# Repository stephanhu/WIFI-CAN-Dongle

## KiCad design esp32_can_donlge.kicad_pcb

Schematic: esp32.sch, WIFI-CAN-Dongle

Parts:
C1, C2, C4: 100n/25V; C_0603_1608Metric
C3, C5: 10u/25V; C_0805_2012Metric
C6, C7: C; C_0603_1608Metric
D1, D2: LED; LED_0805_2012Metric
D3: BAT54C; SOT-23
J1: Conn_01x02_Male; PinHeader_1x02_P2.54mm_Horizontal
J2: DM3AT-SF-PEJM5(40); microSD_HC_Hirose_DM3AT-SF-PEJM5
L1, L2: L; L_0603_1608Metric
Q1: DMG2305UX-7; SOT-23
R1, R2: 1k; R_0603_1608Metric
R3, R4, R5, R6, R7, R8, R15: 10k; R_0603_1608Metric
R9, R11, R12, R13: 33R; R_0603_1608Metric
R10: 10R; R_0603_1608Metric
R14: 200R; R_0603_1608Metric
R16, R17: 220R; R_0603_1608Metric
U1: ESP32-WROOM-32
Y1: LFXTAL009709Bulk; Crystal_SMD_3215-2Pin_3.2x1.5mm

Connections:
+3V3: C4.1, C5.1, Q1.2, R3.1, R4.2, U1.2; also elsewhere on the board
/can_interface/CAN_EN: U1.12; also elsewhere on the board
/can_interface/CAN_RX: R16.2; also elsewhere on the board
/can_interface/CAN_TERM_EN: U1.6; also elsewhere on the board
/can_interface/CAN_TX: R17.2; also elsewhere on the board
/esp32/BOOT: D3.1, J1.1, U1.25
/esp32/DET_A: J2.10, U1.27, U1.37
/esp32/DET_B: R15.2, U1.10, U1.28
/esp32/ESP_EN: C1.1, R3.2, U1.3; also elsewhere on the board
/esp32/IO0: D3.3; also elsewhere on the board
/esp32/SD_CLK: R10.1, U1.13
/esp32/SD_CMD: R6.2, R13.1, U1.23
/esp32/SD_DAT0: R7.2, R14.1, U1.24
/esp32/SD_DAT1: R8.2, R11.1, U1.26
/esp32/SD_DAT2: D3.2, R12.1, U1.14
/esp32/SD_DAT3: R5.2, R9.1, U1.16
/esp32/SD_EN: Q1.1, R4.1, U1.11
/esp32/SD_VDD: C2.1, C3.1, J2.4, L1.1, R5.1, R6.1, R7.1, R8.1
/esp32/TEST_LED0: R1.1, U1.30
/esp32/TEST_LED1: R2.1, U1.31
/usb_uart/RXD: U1.35; also elsewhere on the board
/usb_uart/TXD: U1.34; also elsewhere on the board
BAT_ADC_IN: U1.7; also elsewhere on the board
GND: C1.2, C2.2, C3.2, C4.2, C5.2, C6.1, C7.1, D1.1, D2.1, J1.2, J2.6, L2.1, U1.1, U1.15, U1.38, U1.39; also elsewhere on the board
unnamed: C6.2, U1.8, Y1.1
unnamed: C7.2, U1.9, Y1.2
unnamed: D1.2, R1.2
unnamed: D2.2, R2.2
unnamed: J2.1, R12.2
unnamed: J2.2, R9.2
unnamed: J2.3, R13.2
unnamed: J2.5, R10.2
unnamed: J2.7, R14.2
unnamed: J2.8, R11.2
unnamed: J2.9, R15.1
unnamed: J2.11, L2.2
unnamed: L1.2, Q1.3
unnamed: R16.1, U1.33
unnamed: R17.1, U1.36

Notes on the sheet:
0: SPI Boot 1: Download Boot
using two pins for lower quiescent current
Global Label
Hierachical Label
Local Label
activate internal pullup in user programm on GPIO12

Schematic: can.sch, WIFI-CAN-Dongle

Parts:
C8: 100n/25V; C_0603_1608Metric
C9: 10u/25V; C_0805_2012Metric
R18: 0R; R_0603_1608Metric
R19, R20: 10k; R_0603_1608Metric
R21: 1k; R_0603_1608Metric
R22: 470R; R_0603_1608Metric
R23: 100R; R_0603_1608Metric
U2: SN65HVD230DR; SOIC-8_3.9x4.9mm_P1.27mm
U3: TLP175A; MFSOP6-4_4.4x3.6mm_P1.27mm

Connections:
+3V3: C8.1, C9.1, R19.1, R21.1, U2.3; also elsewhere on the board
/can_interface/CAN_EN: R18.2; also elsewhere on the board
/can_interface/CAN_N: U2.6, U3.4; also elsewhere on the board
/can_interface/CAN_P: R23.1, U2.7; also elsewhere on the board
/can_interface/CAN_RX: U2.4; also elsewhere on the board
/can_interface/CAN_TERM_EN: R22.2; also elsewhere on the board
/can_interface/CAN_TX: U2.1; also elsewhere on the board
GND: C8.2, C9.2, R20.2, U2.2, U3.3; also elsewhere on the board
unnamed: R18.1, R21.2, U2.8
unnamed: R19.2, R20.1, U2.5
unnamed: R22.1, U3.1
unnamed: R23.2, U3.6

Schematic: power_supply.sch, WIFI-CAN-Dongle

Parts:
C10, C15, C16: 10u/25V; C_0805_2012Metric
C11: 1u/25V; C_0603_1608Metric
C12: 10n/25V; C_0603_1608Metric
C13: 100n/25V; C_0603_1608Metric
C14: 10p/50V; C_0603_1608Metric
D4: NUP2105L; SOT-23
D5: B130-E3; D_SMA
J3: DB9_Male; DSUB-9_Male_EdgeMount_P2.77mm
L3: XFL3012-222ME; L_Coilcraft_XLF3012
R24, R32: 1M; R_0603_1608Metric
R25: 120k; R_0603_1608Metric
R26, R31: 82k; R_0603_1608Metric
R27: 33k; R_0603_1608Metric
R28: n.b.; R_0603_1608Metric
R29: 18k; R_0603_1608Metric
R30: 200R; R_0603_1608Metric
R33: 309k; R_0603_1608Metric
U4: LT8607; MSOP-10-1EP_3x3mm_P0.5mm_EP1.68x1.88mm

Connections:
+3V3: C14.1, C15.1, C16.1, L3.2, R31.1, R32.1; also elsewhere on the board
+12V: C10.1, D5.1 (K), R28.2, U4.9
/can_interface/CAN_N: D4.1, J3.2; also elsewhere on the board
/can_interface/CAN_P: D4.2, J3.7; also elsewhere on the board
/power_supply/Power_Good: R31.2, U4.8
/power_supply/V_BAT: D5.2 (A), J3.9, R24.1, R26.1
BAT_ADC_IN: R26.2, R27.1; also elsewhere on the board
GND: C10.2, C11.2, C12.2, C15.2, C16.2, D4.3, J3.3, R25.2, R27.2, R30.2, R33.2, U4.11; also elsewhere on the board
unnamed: C11.1, U4.3
unnamed: C12.1, U4.7
unnamed: C13.1, U4.1
unnamed: C13.2, L3.1, U4.2
unnamed: C14.2, R32.2, R33.1, U4.6
unnamed: R24.2, R25.1, U4.10
unnamed: R28.1, U4.5
unnamed: R29.1, U4.4
unnamed: R29.2, R30.1

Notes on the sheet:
Voltage regulator will be shut down below 9V of V_BAT Vin(en) around 9,33V

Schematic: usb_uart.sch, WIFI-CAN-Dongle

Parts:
C17: 100n/10V; C_0603_1608Metric
C18, C20: 4u7/10V; C_0805_2012Metric
C19: 100n/25V; C_0603_1608Metric
D6, D7: LED; LED_0805_2012Metric
J4: USB_B_Micro; USB_Micro-B_Wuerth_629105150521_CircularHoles
L4: L; L_0603_1608Metric
L5: L; L_0805_2012Metric
Q2, Q3: BC817; SOT-23
R34: 22k; R_0603_1608Metric
R35: 47k; R_0603_1608Metric
R36, R37, R38, R39, R40: 1k; R_0603_1608Metric
U5: USBLC6-2SC6; SOT-23-6
U6: CP2102N-A01-GQFN24; QFN-24-1EP_4x4mm_P0.5mm_EP2.6x2.6mm

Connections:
+5V: C17.1, C18.1, L5.1, R34.1, R36.1, U5.5, U6.7
/esp32/ESP_EN: Q2.3; also elsewhere on the board
/esp32/IO0: Q3.3; also elsewhere on the board
/usb_uart/DTR: Q3.2, R39.2, U6.23
/usb_uart/D_IN_M: U5.3, U6.4
/usb_uart/D_IN_P: U5.1, U6.3
/usb_uart/D_M: J4.2, U5.4
/usb_uart/D_P: J4.3, U5.6
/usb_uart/RTS: Q2.2, R40.2, U6.19
/usb_uart/RXD: U6.20; also elsewhere on the board
/usb_uart/TXD: U6.21; also elsewhere on the board
/usb_uart/VIO: C19.1, C20.1, R37.1, R38.1, U6.5, U6.6
GND: C17.2, C18.2, C19.2, C20.2, J4.5, L4.2, R35.2, U5.2, U6.2, U6.25; also elsewhere on the board
unnamed: D6.1, U6.11
unnamed: D6.2, R37.2
unnamed: D7.1, U6.12
unnamed: D7.2, R38.2
unnamed: J4.1, L5.2
unnamed: J4.6, L4.1
unnamed: Q2.1, R39.1
unnamed: Q3.1, R40.1
unnamed: R34.2, R35.1, U6.8
unnamed: R36.2, U6.9

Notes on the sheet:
3.3V
Auto program
DTR 1 0 1 0
RTS-> 1 0 0 1
EN 1 0 1 0
IO0 1 0 1 0

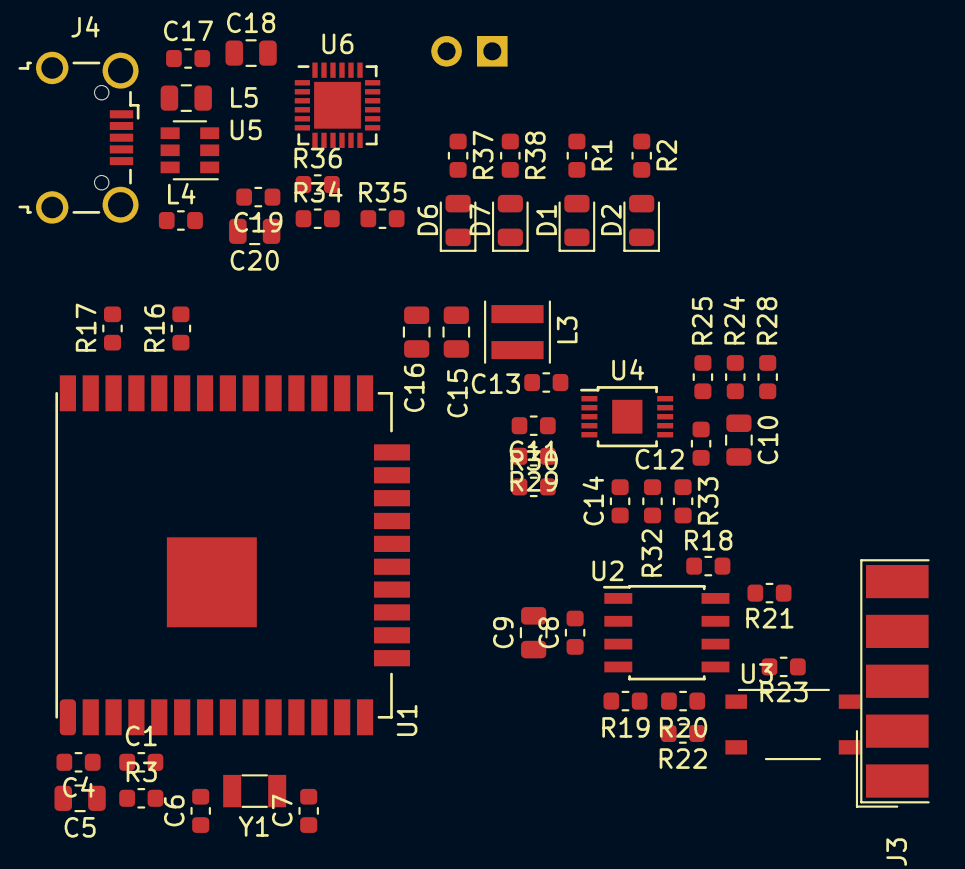
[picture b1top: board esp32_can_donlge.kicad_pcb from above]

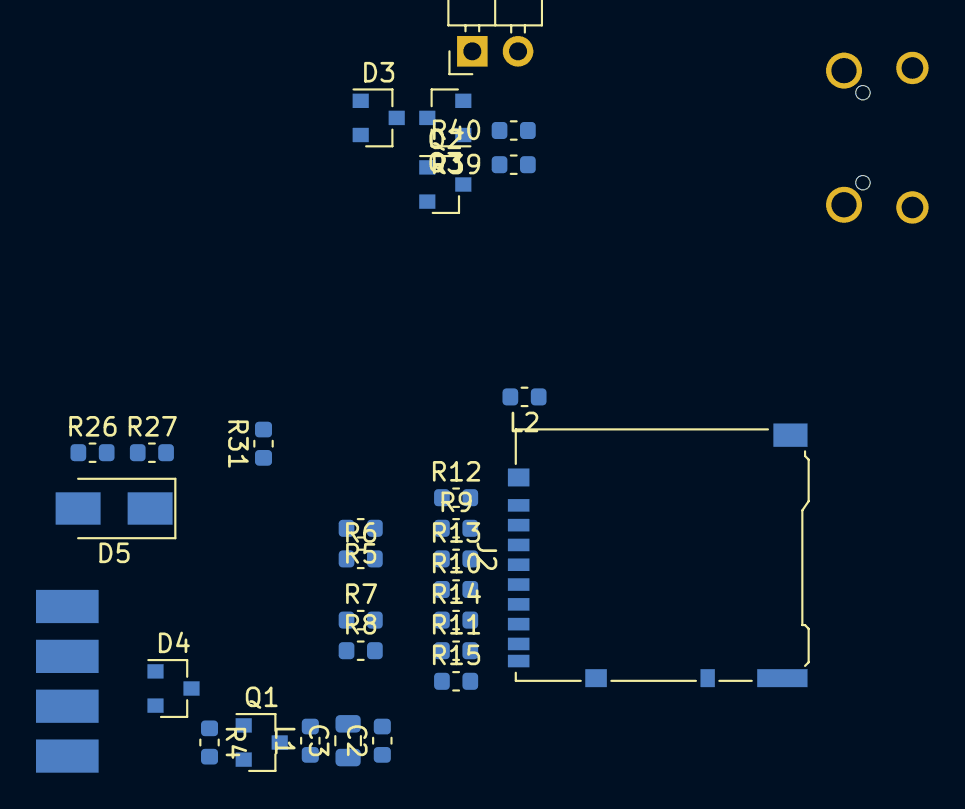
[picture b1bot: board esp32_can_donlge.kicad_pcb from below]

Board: 4 copper layers, 86 parts (29 on the bottom side), 75 nets, no tracks yet.

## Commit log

2018-09-29 init
2018-09-30 added esp32, can, usb-uart
2018-10-03 finished schematic, first placement started
